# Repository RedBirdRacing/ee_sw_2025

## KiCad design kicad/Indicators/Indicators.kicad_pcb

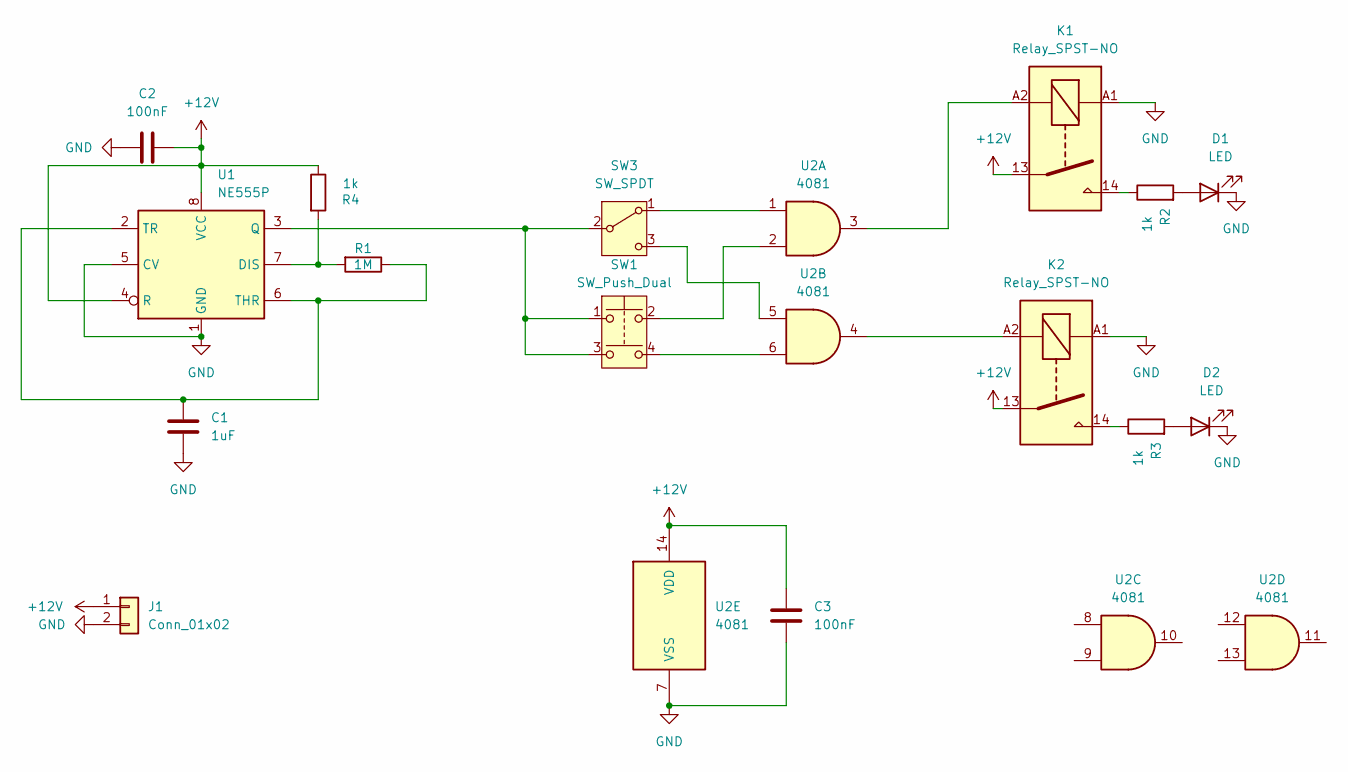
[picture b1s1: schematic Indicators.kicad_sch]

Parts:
C1: 1uF; C_0805_2012Metric_Pad1.18x1.45mm_HandSolder
C2, C3: 100nF; C_0805_2012Metric_Pad1.18x1.45mm_HandSolder
D1, D2: LED; LED_0805_2012Metric_Pad1.15x1.40mm_HandSolder
J1: Conn_01x02; JST_XH_B2B-XH-A_1x02_P2.50mm_Vertical
K1, K2: Relay_SPST-NO; JST_XH_B4B-XH-A_1x04_P2.50mm_Vertical
R1: 1M; R_Axial_DIN0204_L3.6mm_D1.6mm_P5.08mm_Horizontal
R2, R3, R4: 1k; R_Axial_DIN0204_L3.6mm_D1.6mm_P5.08mm_Horizontal
SW1: SW_Push_Dual; JST_XH_B4B-XH-A_1x04_P2.50mm_Vertical
SW3: SW_SPDT; JST_XH_B3B-XH-A_1x03_P2.50mm_Vertical
U1: NE555P; DIP-8_W7.62mm
U2: 4081; DIP-14_W7.62mm

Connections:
+12V: C2.2, C3.2, J1.1, K1.13, K2.13, R4.1, U1.4 (R), U1.8 (VCC), U2.14 (VDD)
GND: C1.2, C2.1, C3.1, D1.1 (K), D2.1 (K), J1.2, K1.A1, K2.A1, U1.1 (GND), U1.5 (CV), U2.7 (VSS)
unnamed: D1.2 (A), R2.2
unnamed: D2.2 (A), R3.2
unnamed: K1.14, R2.1
unnamed: K1.A2, U2.3
unnamed: K2.14, R3.1
unnamed: K2.A2, U2.4
unnamed: SW1.2, U2.2
unnamed: SW1.4, U2.6
unnamed: SW3.1 (A), U2.1
unnamed: SW1.1, SW1.3, SW3.2 (B), U1.3 (Q)
unnamed: SW3.3 (C), U2.5
unnamed: R1.2, R4.2, U1.7 (DIS)
unnamed: C1.1, R1.1, U1.2 (TR), U1.6 (THR)

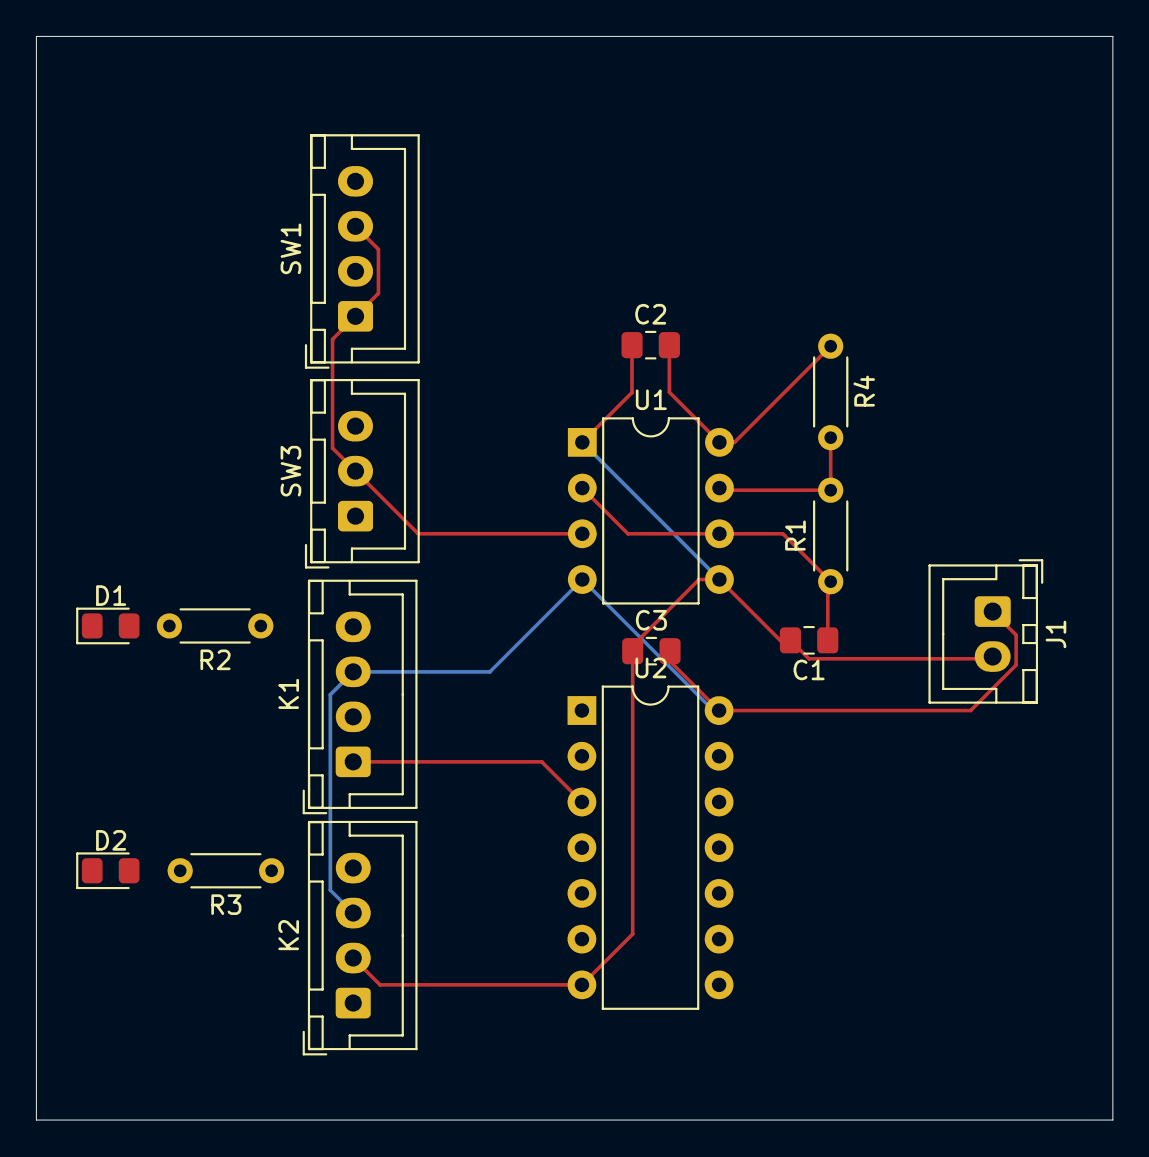
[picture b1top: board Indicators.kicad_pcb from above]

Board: 2 copper layers, 59.8 x 60.2 mm, 16 parts (0 on the bottom side), 15 nets.

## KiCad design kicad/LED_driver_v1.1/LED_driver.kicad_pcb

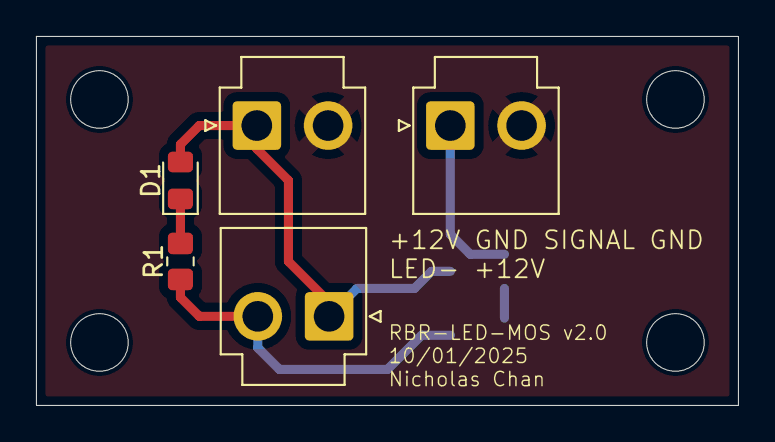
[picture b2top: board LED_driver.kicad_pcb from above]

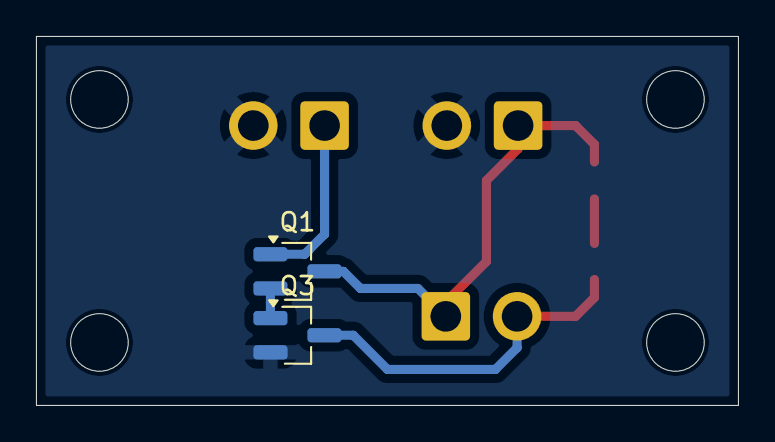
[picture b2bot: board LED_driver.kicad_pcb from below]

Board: 2 copper layers, 39.0 x 20.5 mm, 11 parts (2 on the bottom side), 6 nets.

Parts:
D1: LED; LED_0805_2012Metric_Pad1.15x1.40mm_HandSolder
H1, H2, H3, H4: MountingHole; MountingHole_3.2mm_M3
J1, J2, J3: Conn_01x02; JST_VH_B2P-VH_1x02_P3.96mm_Vertical
Q1: MMBT3904; SOT-23_Handsoldering
Q3: 2N7002; SOT-23_Handsoldering
R1: 1k; R_0805_2012Metric_Pad1.20x1.40mm_HandSolder

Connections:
+12V: D1.2 (A), J1.1, J3.1, Q1.3 (C)
/LED-: J3.2, Q3.3 (D), R1.2
/SIGNAL: J2.1, Q1.1 (B)
GND: J1.2, J2.2, Q3.2 (S)
unnamed: D1.1 (K), R1.1
unnamed: Q1.2 (E), Q3.1 (G)

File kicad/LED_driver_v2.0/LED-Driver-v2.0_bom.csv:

"Value","Footprint","Qty"
"LED","LED_SMD:LED_0805_2012Metric_Pad1.15x1.40mm_HandSolder","1"
"Conn_01x02","Connector_JST:JST_VH_B2P-VH_1x02_P3.96mm_Vertical","3"
"MMBT3904","Package_TO_SOT_SMD:SOT-23_Handsoldering","1"
"2N7002","Package_TO_SOT_SMD:SOT-23_Handsoldering","1"
"1k","Resistor_SMD:R_0805_2012Metric_Pad1.20x1.40mm_HandSolder","1"

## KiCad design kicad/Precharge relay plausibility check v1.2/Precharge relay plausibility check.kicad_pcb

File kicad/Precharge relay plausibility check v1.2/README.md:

v1.2 changed screw holes from M2 to M3 by Nicholas

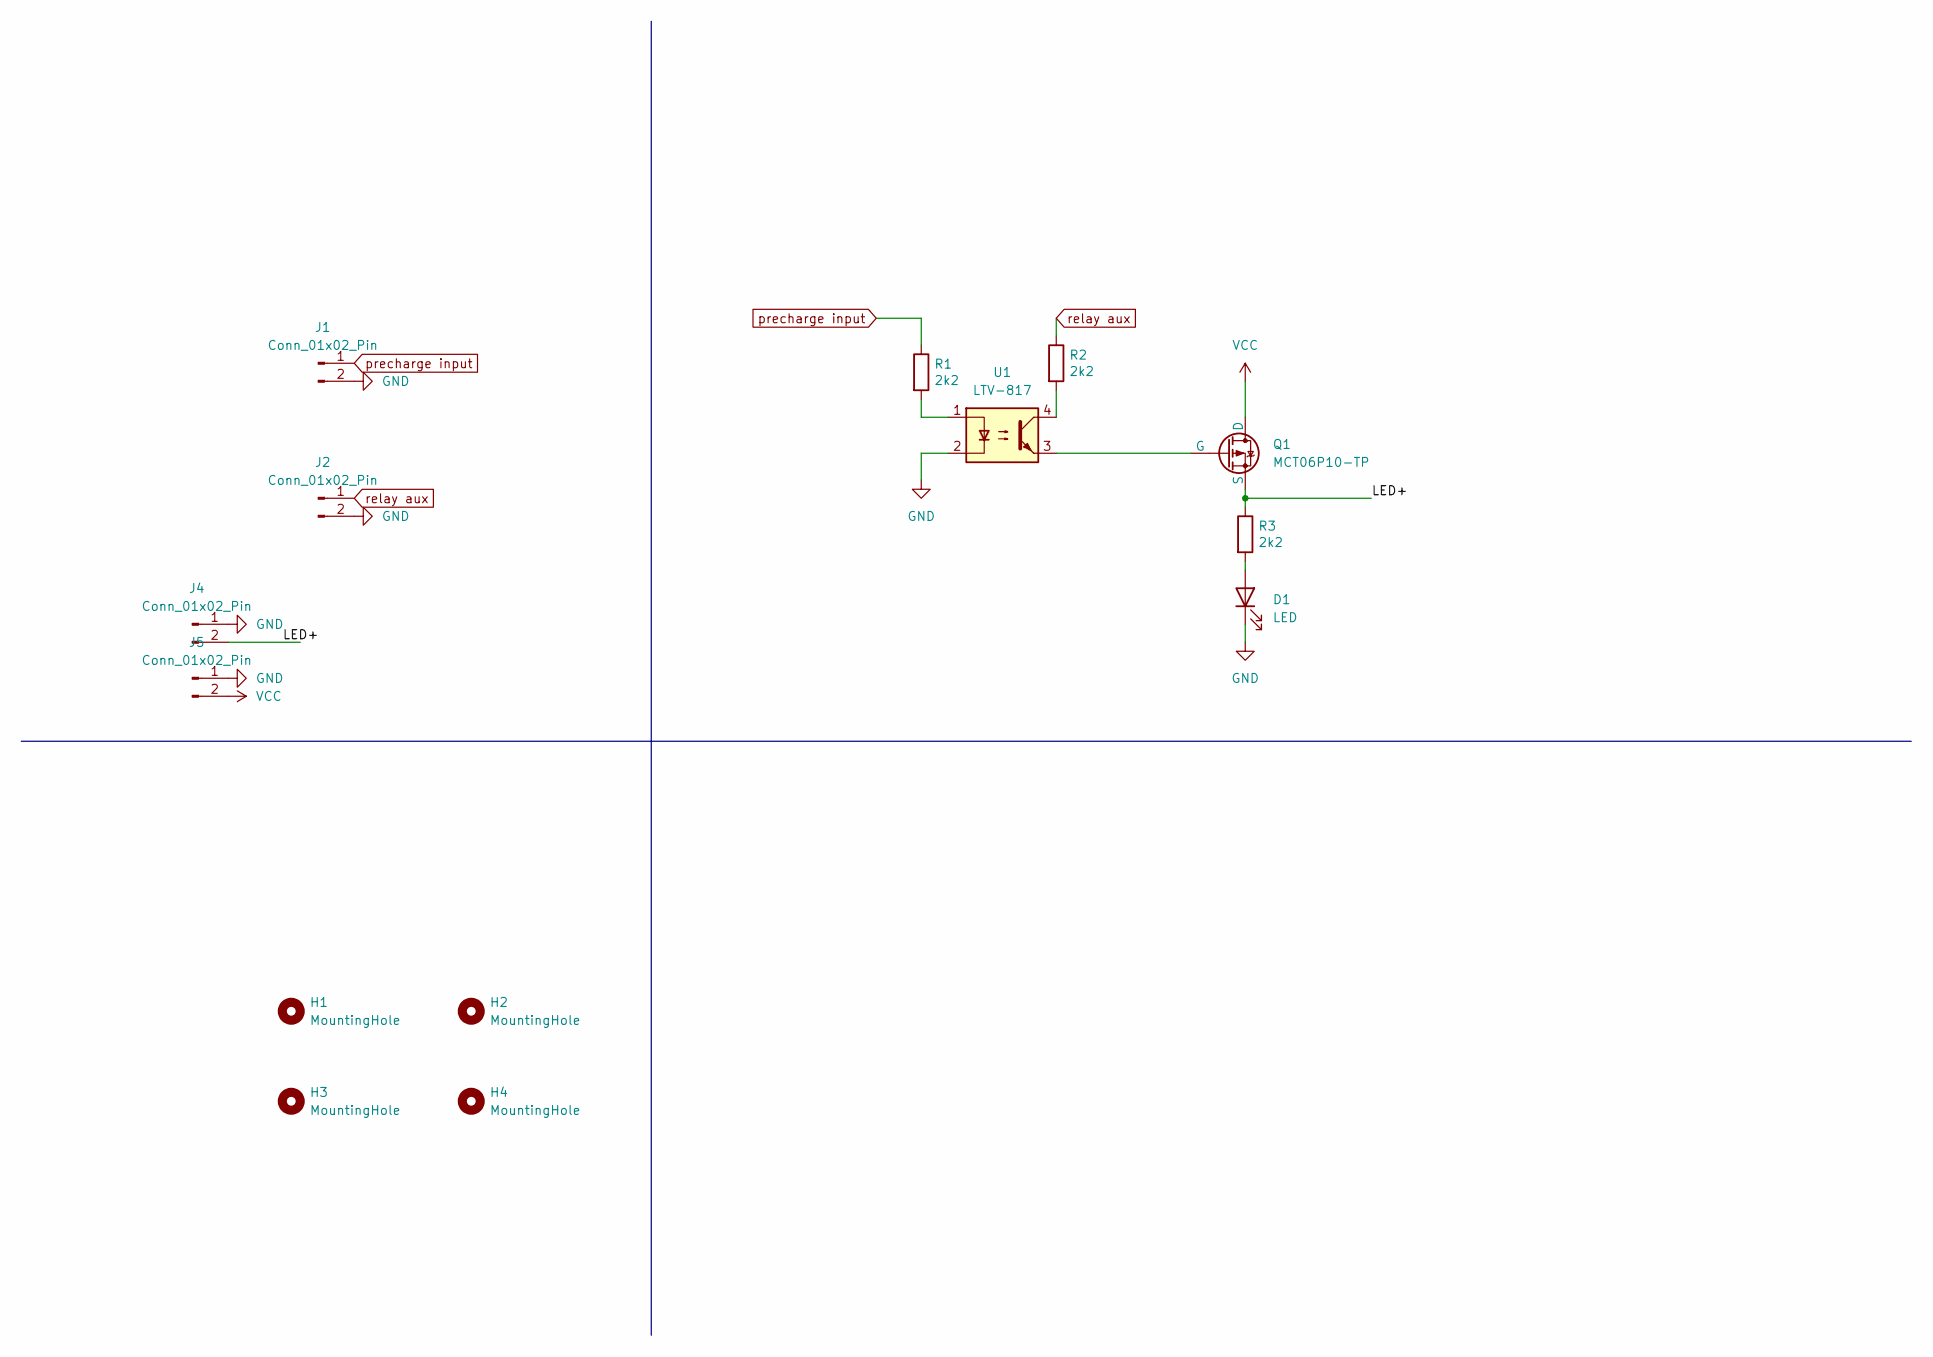
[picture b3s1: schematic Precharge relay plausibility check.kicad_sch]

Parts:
D1: LED; LED_0805_2012Metric_Pad1.15x1.40mm_HandSolder
H1, H2, H3, H4: MountingHole; MountingHole_3.2mm_M3
J1, J2, J4, J5: Conn_01x02_Pin; JST_VH_B2P-VH_1x02_P3.96mm_Vertical
Q1: MCT06P10-TP; SOT-223-3_TabPin2
R1, R2, R3: 2k2; R_0805_2012Metric_Pad1.20x1.40mm_HandSolder
U1: LTV-817; DIP-4_W7.62mm

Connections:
/LED+: J4.2, Q1.3 (S), R3.1
GND: D1.1 (K), J1.2, J2.2, J4.1, J5.1, U1.2
unnamed: D1.2 (A), R3.2
unnamed: Q1.2 (G), U1.3
unnamed: R1.2, U1.1
unnamed: R2.2, U1.4
VCC: J5.2, Q1.1 (D)
precharge input: J1.1, R1.1
relay aux: J2.1, R2.1

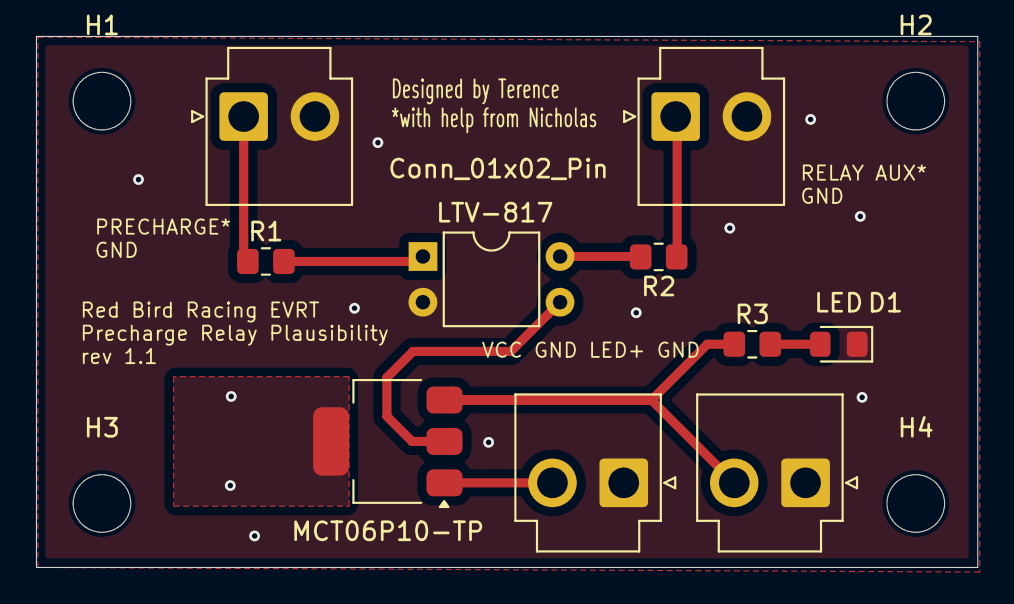
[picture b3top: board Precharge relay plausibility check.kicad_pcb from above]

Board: 2 copper layers, 52.3 x 29.5 mm, 14 parts (0 on the bottom side), 9 nets.

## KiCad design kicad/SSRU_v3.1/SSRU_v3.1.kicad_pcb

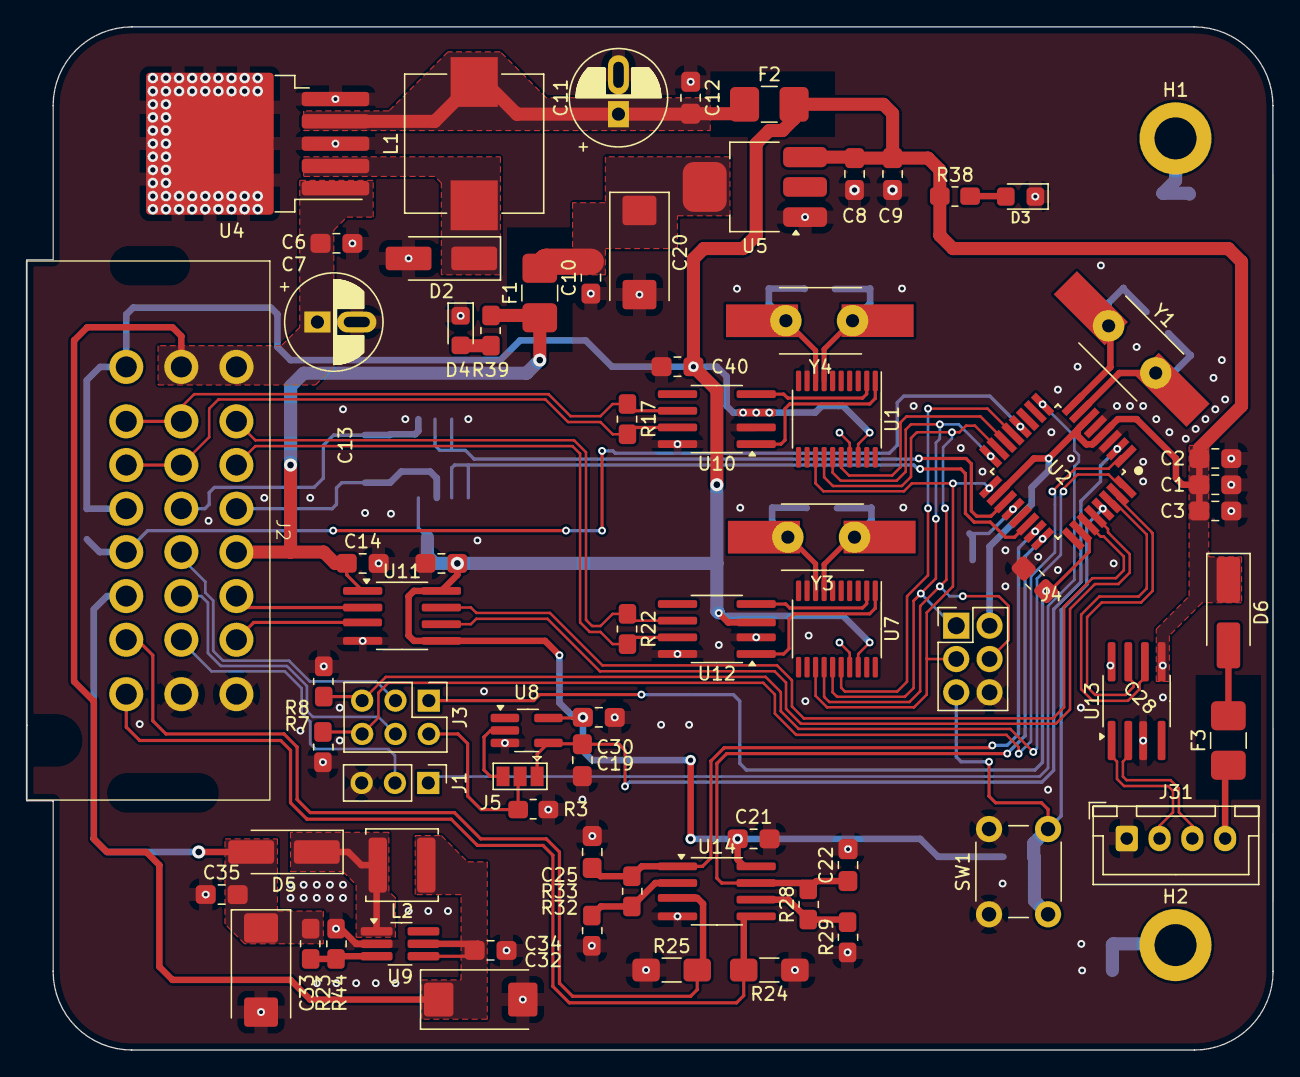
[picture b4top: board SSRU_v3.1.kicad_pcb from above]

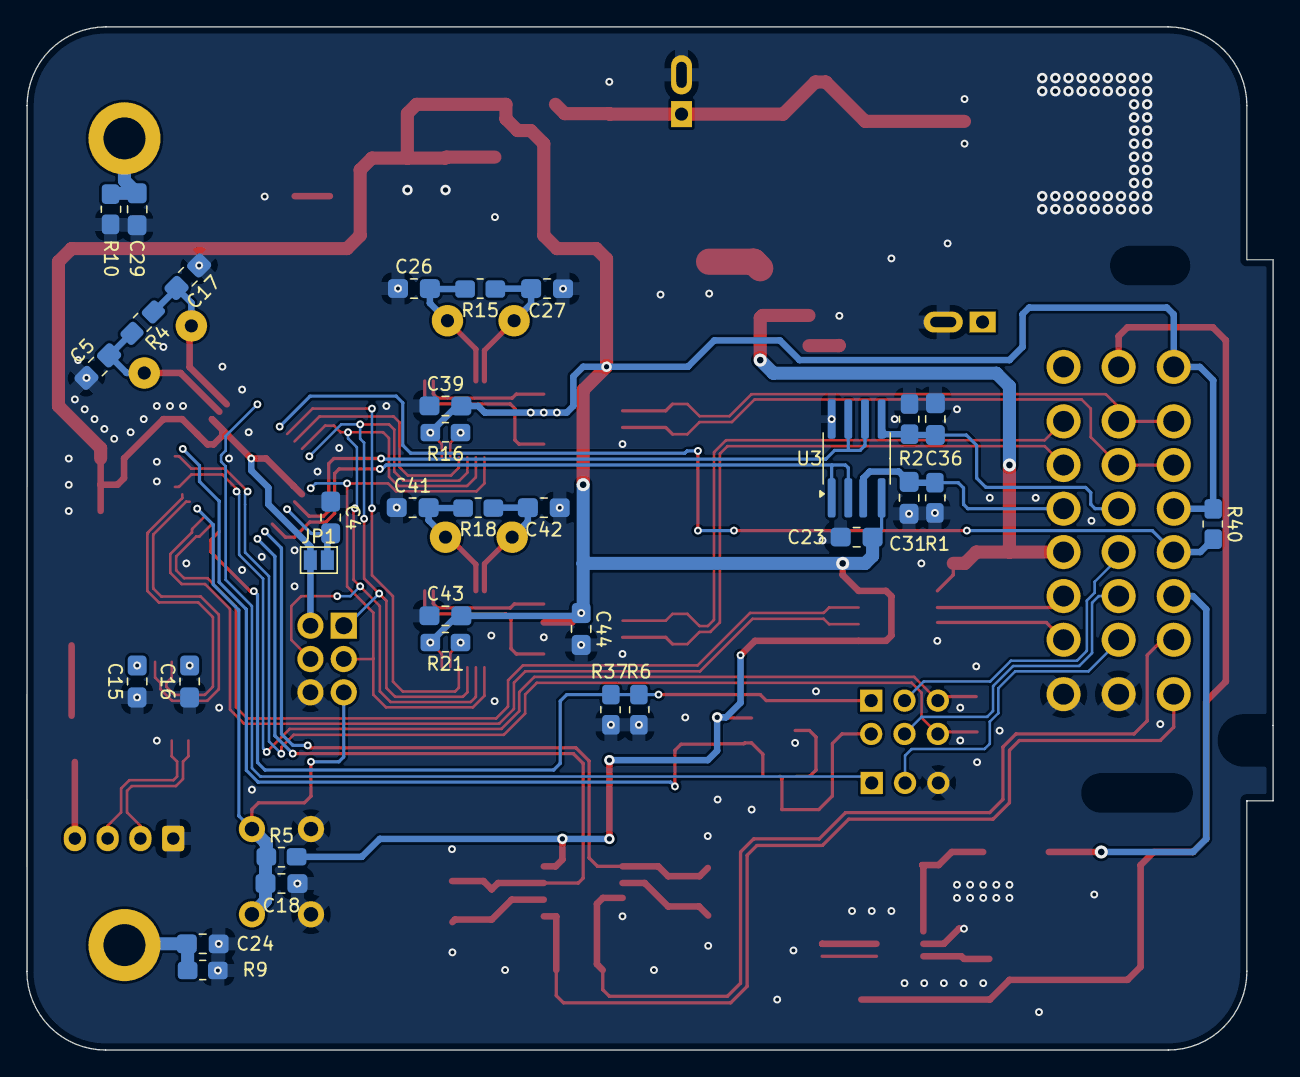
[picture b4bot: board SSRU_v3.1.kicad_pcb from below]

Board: 2 copper layers, 95.0 x 78.0 mm, 106 parts (33 on the bottom side), 69 nets.

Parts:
C1, C3, C4, C6, C8, C10, C12, C13, C14, C15, C16, C21, C22, C23, C24, C25, C28, C29, C30, C31, C34, C35, C36, C39, C40, C43, C44: 100nF; C_0805_2012Metric_Pad1.18x1.45mm_HandSolder_L
C2, C9, C18: 10uF; C_0805_2012Metric_Pad1.18x1.45mm_HandSolder_L
C5, C17, C26, C27, C41, C42: 22pF; C_0805_2012Metric_Pad1.18x1.45mm_HandSolder_L
C7: 100uF; CP_Radial_D6.3mm_P2.50mm_handsolder
C11: 330uF; CP_Radial_D6.3mm_P2.50mm_handsolder
C19: optional; C_0805_2012Metric_Pad1.18x1.45mm_HandSolder_L
C20, C32, C33: 22uF; CP_EIA-7343-30_AVX-N_HandSolder
D2, D5, D6: SMA Diode; D_SMA_Handsoldering
D3, D4: LED; LED_0805_2012Metric_Pad1.45x1.40mm_HandSolder
F1, F2, F3: Fuse; Fuse_1210_3225Metric_Pad1.42x2.65mm_HandSolder
H1, H2: MountingHole_Pad; MountingHole_3.2mm_M3_ISO14580_Pad
J1: Conn_01x03; PinHeader_1x03_P2.54mm_Vertical
J2: Conn_01x24; HD241_24pin
J3: Conn_02x03_Odd_Even; PinHeader_2x03_P2.54mm_Vertical
J4: AVR-ISP-6; PinHeader_2x03_P2.54mm_Vertical
J5: Conn_01x03; SolderJumper-3_P1.3mm_Open_Pad1.0x1.5mm
J31: Conn_01x04; JST_XH_B4B-XH-A_1x04_P2.50mm_Vertical
JP1: Jumper_2_Open; SolderJumper-2_P1.3mm_Open_Pad1.0x1.5mm
L1: 330uH; L_10.4x10.4_H4.8
L2: 4.7-22uH; L_Sunlord_SWPA5040S
R1, R2, R3, R6, R7, R8, R9, R10: 1M; R_0805_2012Metric_Pad1.20x1.40mm_HandSolder_L
R4, R15, R18: 10M; R_0805_2012Metric_Pad1.20x1.40mm_HandSolder_L
R5: 4.7k; R_0805_2012Metric_Pad1.20x1.40mm_HandSolder_L
R16, R21: 10k; R_0805_2012Metric_Pad1.20x1.40mm_HandSolder_L
R17, R22, R39: 120R; R_0805_2012Metric_Pad1.20x1.40mm_HandSolder_L
R23: 249k; R_0805_2012Metric_Pad1.20x1.40mm_HandSolder_L
R24, R25: 10R; R_1206_3216Metric_Pad1.30x1.75mm_HandSolder_RMC
R28, R33: 22k; R_0805_2012Metric_Pad1.20x1.40mm_HandSolder_L
R29, R32: 1k; R_0805_2012Metric_Pad1.20x1.40mm_HandSolder_L
R37: 50k; R_0805_2012Metric_Pad1.20x1.40mm_HandSolder_L
R38: 330R; R_0805_2012Metric_Pad1.20x1.40mm_HandSolder_L
R40: 4k7; R_0805_2012Metric_Pad1.20x1.40mm_HandSolder_L
R44: 680R; R_0805_2012Metric_Pad1.20x1.40mm_HandSolder_L
SW1: SW_Push; SW_PUSH_6mm_H5mm
U1, U7: MCP2515-xSO; TSSOP-20_4.4x6.5mm_P0.65mm
U2: ATmega328P-A; TQFP-32_7x7mm_P0.8mm_L
U3, U14: LM2904; SOIC-8_3.9x4.9mm_P1.27mm_RMC_Handsolder
U4: LM2576S-5; TO-263-5_TabPin3_Handsolder
U5: AMS1117-3.3; SOT-223-3_TabPin2_Handsolder
U8: 74LVC1G17; SOT-23-5_HandSoldering_Extended_RMC
U9: MT3608/SDB628; SOT-23-6_Handsoldering_Extended_RMC
U10, U12: TJA1051T; SOIC-8_3.9x4.9mm_P1.27mm_RMC_Handsolder
U11: TCA9517D; SOIC-8_3.9x4.9mm_P1.27mm_RMC_Handsolder
U13: CH340N; SOIC-8_3.9x4.9mm_P1.27mm_RMC_Handsolder
Y1: 16MHz; Crystal_HC49-U_Vertical_W_SMD
Y3, Y4: 20MHz; Crystal_HC49-U_Vertical_W_SMD

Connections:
328+: U2.30 (PD0), U13.6 (TXD)
328-: U2.31 (PD1), U13.7 (RXD)
+3.3V: C14.1, F1.1, J2.5, R39.1, U11.1 (VCCA)
+5V: C1.2, C2.2, C3.2, C8.2, C9.2, C13.2, C15.2, C21.1, C23.2, C30.2, C39.2, C40.1, C43.2, C44.1, D6.1 (K), F2.2, J2.17, J2.20, J4.2 (VCC), JP1.1 (A), R5.2, R16.2, R21.2, R38.1, R40.1, U1.18 (VDD), U2.4 (VCC), U2.6 (VCC), U2.18 (AVCC), U3.4 (V-), U5.3 (VI), U7.18 (VDD), U8.5 (VCC), U10.3 (VCC), U11.5 (EN), U11.8 (VCCB), U12.3 (VCC), U13.5 (VCC), U14.8 (V+)
+12V: C6.2, C7.1, C32.1, C34.2, J2.1, J2.9, L2.1, U4.1 (VIN), U9.4 (EN), U9.5 (IN)
+24V: C33.1, C35.2, D5.2 (A), J2.22, R23.1
BRAKE_TEMP1: J2.23, R25.2, U14.3 (+)
BRAKE_TEMP2: J2.24, R24.2, U14.5 (+)
BRAKE_TEMP_OUT1: C25.1, R33.2, U2.23 (PC0), U14.1
BRAKE_TEMP_OUT2: C22.1, R28.2, U2.24 (PC1), U14.7
CAN1+: J2.11, J2.19, R17.2, U10.7 (CANH)
CAN1-: J2.10, J2.18, R17.1, U10.6 (CANL)
CAN2+: J2.3, R22.2, U12.7 (CANH)
CAN2-: J2.2, R22.1, U12.6 (CANL)
CS_CAN1: U1.16 (~CS), U2.14 (PB2)
CS_CAN2: U2.13 (PB1), U7.16 (~CS)
DS18B20: J2.21, R40.2, U2.12 (PB0)
ENCODER+: J3.5, R8.2, U2.32 (PD2)
ENCODER-: J3.6, R7.2, U2.1 (PD3)
FLOW_IN: J3.2, J5.2, R3.2
FLOW_OUT: C19.2, J5.1, U2.2 (PD4), U8.4
GND: C1.1, C2.1, C3.1, C4.1, C5.1, C6.1, C7.2, C8.1, C9.1, C10.1, C11.2, C12.1, C13.1, C14.2, C15.1, C16.1, C17.1, C18.1, C19.1, C20.2, C21.2, C22.2, C23.1, C24.1, C25.2, C26.1, C27.1, C28.2, C29.1, C30.1, C31.1, C32.2, C33.2, C34.1, C35.1, C36.1, C39.1, C40.2, C41.1, C42.1, C43.1, C44.2, D2.2 (A), D3.1 (K), D4.1 (K), J1.3, J2.8, J2.16, J4.6 (GND), J31.1, R1.1, R2.1, R3.1, R6.1, R7.1, R8.1, R9.1, R10.1, R24.1, R25.1, R29.1, R32.1, R37.2, R44.2, SW1.1, U1.9 (VSS), U2.3 (GND), U2.5 (GND), U2.21 (GND), U3.8 (V+), U4.3 (GND), U4.5 (~ON/OFF), U5.1 (GND), U7.9 (VSS), U8.3 (GND), U9.2 (GND), U10.2 (GND), U10.8 (S), U11.4 (GND), U12.2 (GND), U12.8 (S), U13.3 (GND), U14.4 (V-)
GND1: C29.2, H1.1, R10.2
GND2: C24.2, H2.1, R9.2
I2C+: U2.27 (PC4), U11.7 (SCLB)
I2C-: U2.28 (PC5), U11.6 (SDAB)
MISO: J4.1 (MISO), U1.15 (SO), U2.16 (PB4), U7.15 (SO)
MOSI: J4.4 (MOSI), U1.14 (SI), U2.15 (PB3), U7.14 (SI)
unnamed: C10.2, C20.1, F1.2, U5.2 (VO)
unnamed: D2.1 (K), L1.1, U4.2 (OUT)
unnamed: D3.2 (A), R38.2
unnamed: D4.2 (A), R39.2
unnamed: D5.1 (K), L2.2, U9.1 (SW)
unnamed: D6.2 (A), F3.2
unnamed: J5.3, U8.2
unnamed: F3.1, J31.4
unnamed: C4.2, JP1.2 (B), U2.20 (AREF)
unnamed: C27.2, R15.1, U1.8 (OSC1), Y4.2
unnamed: C26.2, R15.2, U1.7 (OSC2), Y4.1
unnamed: U1.2 (RXCAN), U10.4 (RXD)
unnamed: U1.1 (TXCAN), U10.1 (TXD)
unnamed: R16.1, U1.17 (~RESET)
unnamed: C11.1, C12.2, F2.1, L1.2, U4.4 (FB)
unnamed: C42.2, R18.1, U7.8 (OSC1), Y3.2
unnamed: C41.2, R18.2, U7.7 (OSC2), Y3.1
unnamed: R21.1, U7.17 (~RESET)
unnamed: R23.2, R44.1, U9.3 (FB)
unnamed: U7.2 (RXCAN), U12.4 (RXD)
unnamed: U7.1 (TXCAN), U12.1 (TXD)
unnamed: C16.2, U13.8 (V3)
unnamed: R32.2, R33.1, U14.2 (-)
unnamed: R28.1, R29.2, U14.6 (-)
POT1_IN: C31.2, J2.4, R1.2, U3.3 (+)
POT1_OUT: U2.22 (ADC7), U3.1, U3.2 (-)
POT2_IN: C36.2, J2.12, R2.2, U3.5 (+)
POT2_OUT: U2.19 (ADC6), U3.6 (-), U3.7
PUMP_NTC_50k: C28.1, J3.1, R6.2, R37.1, U2.26 (PC3)
PUMP_PWM: J1.1, U2.9 (PD5)
RST: C18.2, J4.5 (~RST), R5.1, SW1.2, U2.29 (~RESET/PC6)
SCK: J4.3 (SCK), U1.13 (SCK), U2.17 (PB5), U7.13 (SCK)
SCL_3V3: J2.6, U11.2 (SCLA)
SDA_3V3: J2.7, U11.3 (SDAA)
UD+: J31.2, U13.1 (UD+)
UD-: J31.3, U13.2 (UD-)
XTAL1: C5.2, R4.2, U2.7 (XTAL1/PB6), Y1.2
XTAL2: C17.2, R4.1, U2.8 (XTAL2/PB7), Y1.1
j1: J2.13, J3.3
j2: J2.14, J3.4
j3: J1.2, J2.15

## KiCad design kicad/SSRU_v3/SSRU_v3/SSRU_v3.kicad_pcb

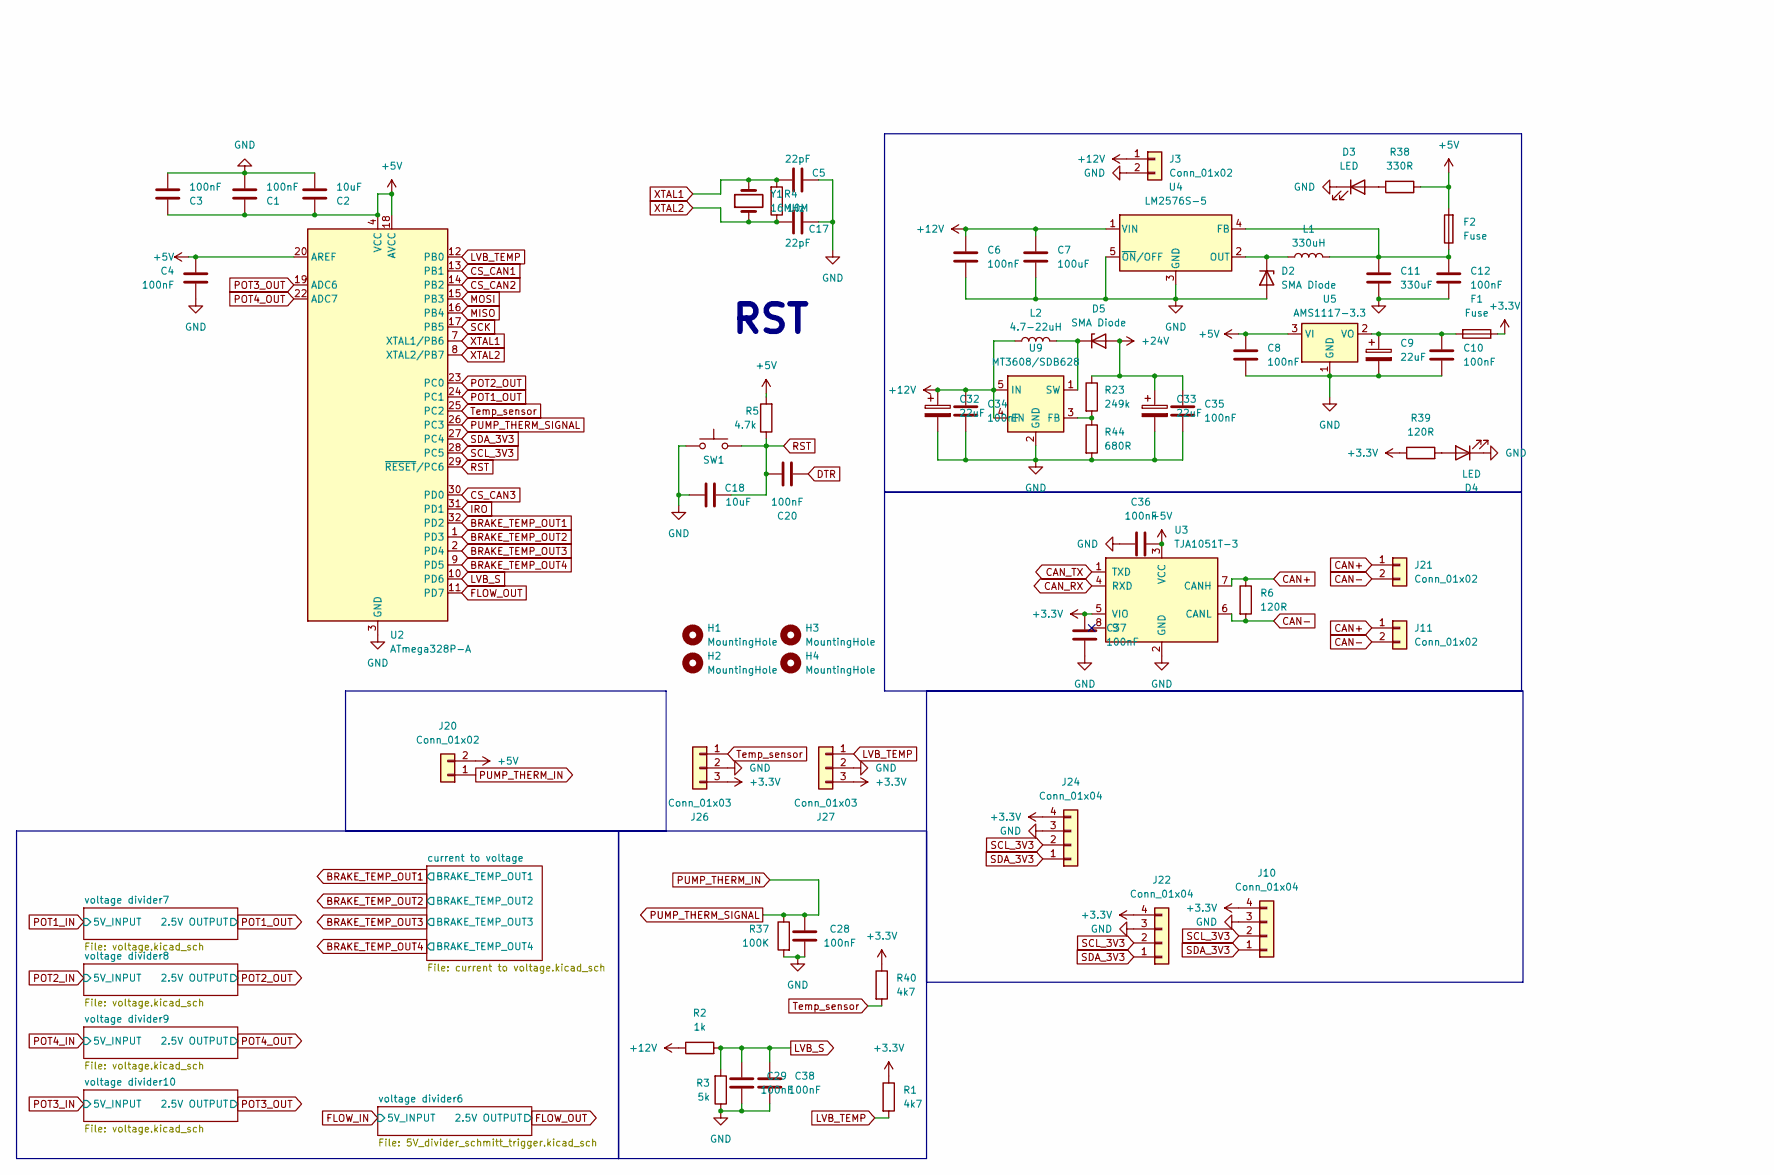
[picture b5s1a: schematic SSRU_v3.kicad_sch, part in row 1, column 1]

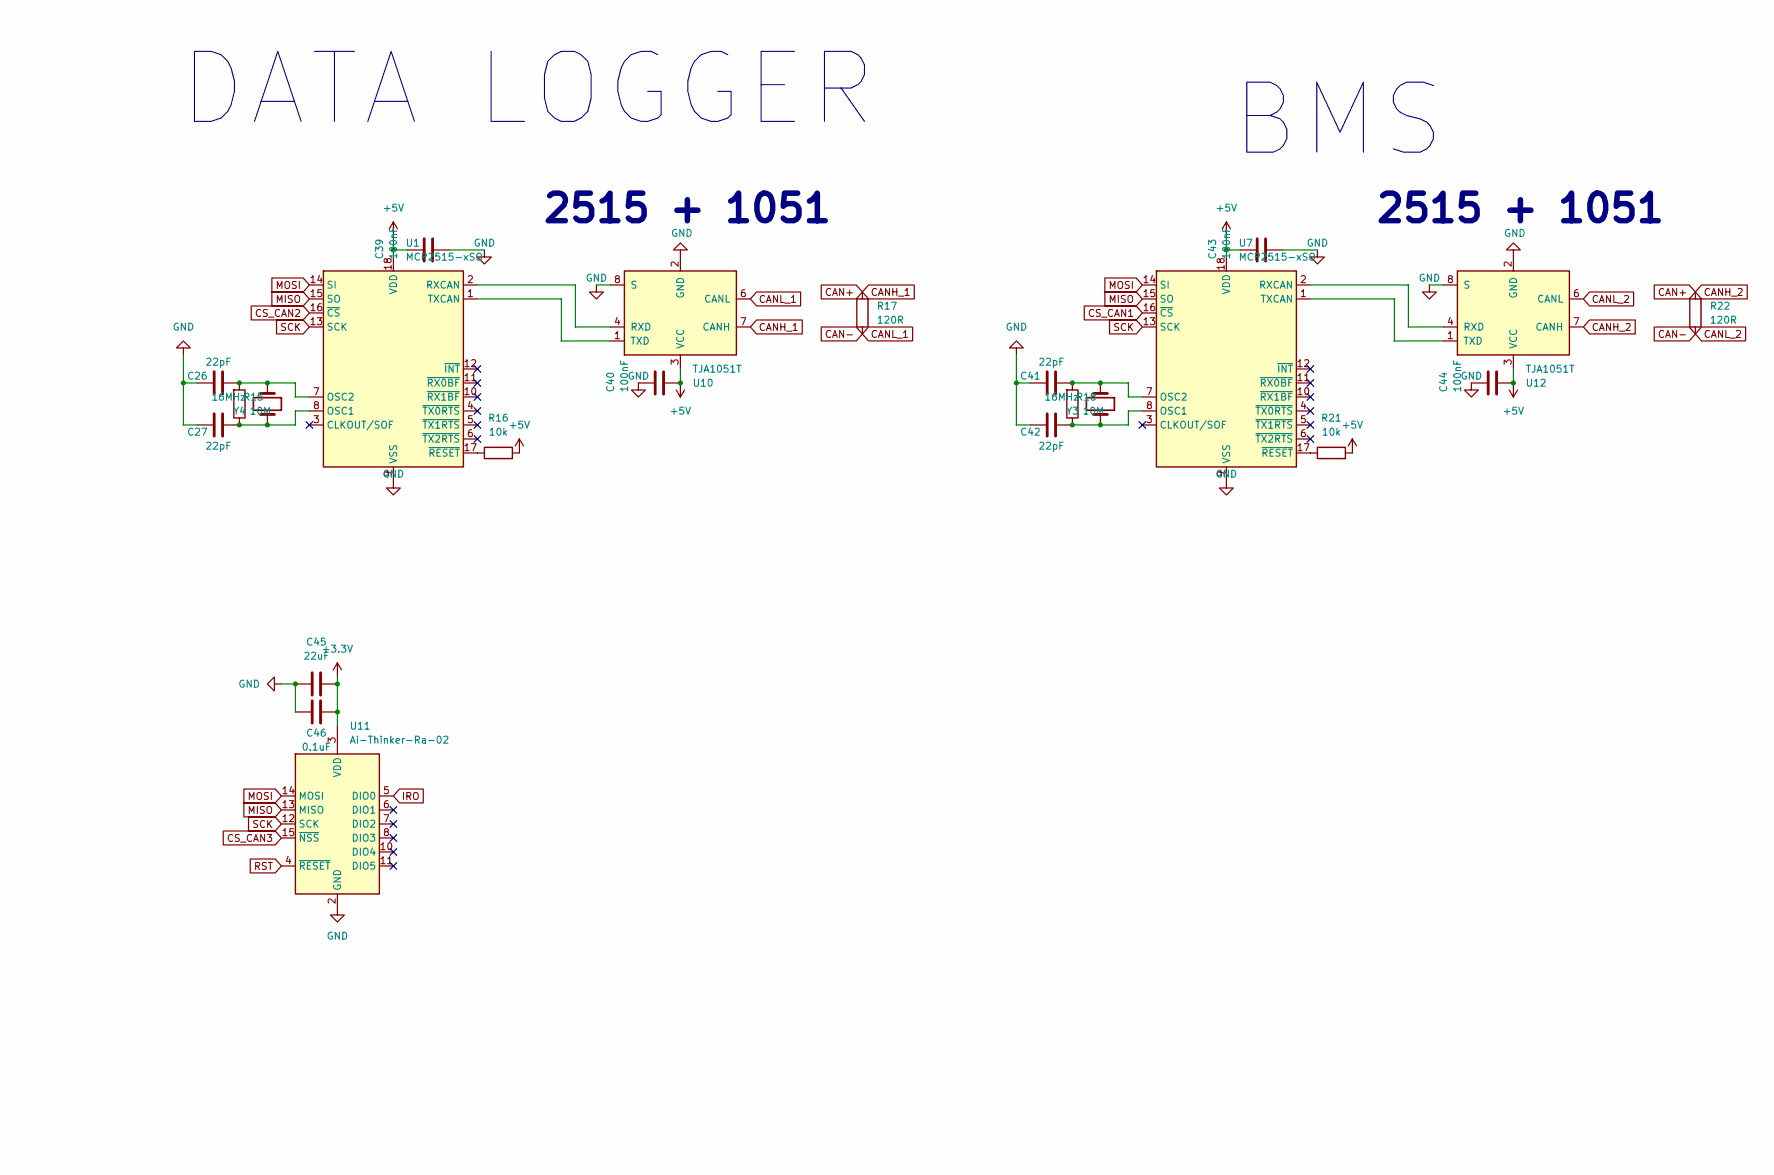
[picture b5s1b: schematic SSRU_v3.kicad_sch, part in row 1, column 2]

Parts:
C1, C3, C4, C6, C8, C10, C12, C20, C28, C29, C34, C35, C36, C37, C38, C39, C40, C43, C44: 100nF; C_0805_2012Metric_Pad1.18x1.45mm_HandSolder_L
C2, C18: 10uF; C_0805_2012Metric_Pad1.18x1.45mm_HandSolder_L
C5, C17, C26, C27, C41, C42: 22pF; C_0805_2012Metric_Pad1.18x1.45mm_HandSolder_L
C7: 100uF; CP_Radial_D6.3mm_P2.50mm
C9, C45: 22uF; C_0805_2012Metric_Pad1.18x1.45mm_HandSolder_L
C11: 330uF; CP_Radial_D6.3mm_P2.50mm
C32, C33: 22uF; CP_EIA-3528-15_AVX-H_Pad1.50x2.35mm_HandSolder_RMC
C46: 0.1uF; C_0805_2012Metric_Pad1.18x1.45mm_HandSolder_L
D2, D5: SMA Diode; D_SMA_Handsoldering
D3, D4: LED; LED_0805_2012Metric_Pad1.45x1.40mm_HandSolder
F1, F2: Fuse; Fuse_1210_3225Metric_Pad1.42x2.65mm_HandSolder
H1, H2, H3, H4: MountingHole; MountingHole_3.2mm_M3
J3: Conn_01x02; JST_VH_B2P-VH_1x02_P3.96mm_Vertical
J10, J22, J24: Conn_01x04; JST_XH_B4B-XH-A_1x04_P2.50mm_Vertical
J11, J20, J21: Conn_01x02; JST_XH_B2B-XH-A_1x02_P2.50mm_Vertical
J26, J27: Conn_01x03; JST_XH_B3B-XH-A_1x03_P2.50mm_Vertical
L1: 330uH; L_10.4x10.4_H4.8
L2: 4.7-22uH; L_Wuerth_HCI-5040
R1, R40: 4k7; R_0805_2012Metric_Pad1.20x1.40mm_HandSolder_L
R2: 1k; R_0805_2012Metric_Pad1.20x1.40mm_HandSolder_L
R3: 5k; R_0805_2012Metric_Pad1.20x1.40mm_HandSolder_L
R4, R15, R18: 10M; R_0805_2012Metric_Pad1.20x1.40mm_HandSolder_L
R5: 4.7k; R_0805_2012Metric_Pad1.20x1.40mm_HandSolder_L
R6, R17, R22, R39: 120R; R_0805_2012Metric_Pad1.20x1.40mm_HandSolder_L
R16, R21: 10k; R_0805_2012Metric_Pad1.20x1.40mm_HandSolder_L
R23: 249k; R_0805_2012Metric_Pad1.20x1.40mm_HandSolder_L
R37: 100K; R_0805_2012Metric_Pad1.20x1.40mm_HandSolder_L
R38: 330R; R_0805_2012Metric_Pad1.20x1.40mm_HandSolder_L
R44: 680R; R_0805_2012Metric_Pad1.20x1.40mm_HandSolder_L
SW1: SW_Push; SW_PUSH_6mm_H5mm
U1, U7: MCP2515-xSO; TSSOP-20_4.4x6.5mm_P0.65mm
U2: ATmega328P-A; TQFP-32_7x7mm_P0.8mm
U3: TJA1051T-3; SOIC-8_3.9x4.9mm_P1.27mm_RMC_Handsolder
U4: LM2576S-5; TO-263-5_TabPin3_Handsolder
U5: AMS1117-3.3; SOT-223-3_TabPin2_Handsolder
U9: MT3608/SDB628; SOT-23-6_Handsoldering
U10, U12: TJA1051T; SOIC-8_3.9x4.9mm_P1.27mm_RMC_Handsolder
U11: Ai-Thinker-Ra-02; Ai-Thinker-Ra-01-LoRa
Y1, Y3, Y4: 16MHz; Crystal_HC49-U_Vertical_W_SMD

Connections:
+3.3V: C37.2, C45.2, C46.1, F1.1, J10.4, J22.4, J24.4, J26.3, J27.3, R1.1, R39.1, R40.1, U3.5 (VIO), U11.3 (VDD); also elsewhere on the board
+5V: C1.2, C2.2, C3.2, C4.2, C8.2, C36.1, C39.2, C40.1, C43.2, C44.1, F2.2, J20.2, R5.2, R16.2, R21.2, R38.1, U1.18 (VDD), U2.4 (VCC), U2.6 (VCC), U2.18 (AVCC), U2.20 (AREF), U3.3 (VCC), U5.3 (VI), U7.18 (VDD), U10.3 (VCC), U12.3 (VCC); also elsewhere on the board
+12V: C6.2, C7.1, C32.1, C34.2, J3.1, L2.1, R2.1, U4.1 (VIN), U9.4 (EN), U9.5 (IN)
+24V: C33.1, C35.2, D5.2 (A), R23.1; also elsewhere on the board
BRAKE_TEMP_OUT1: U2.32 (PD2); also elsewhere on the board
BRAKE_TEMP_OUT2: U2.1 (PD3); also elsewhere on the board
BRAKE_TEMP_OUT3: U2.2 (PD4); also elsewhere on the board
BRAKE_TEMP_OUT4: U2.9 (PD5); also elsewhere on the board
CAN+: J11.1, J21.1, R6.1, R17.2, R22.2, U3.7 (CANH), U10.7 (CANH), U12.7 (CANH)
CAN-: J11.2, J21.2, R6.2, R17.1, R22.1, U3.6 (CANL), U10.6 (CANL), U12.6 (CANL)
CAN_RX: U3.4 (RXD)
CAN_TX: U3.1 (TXD)
CS_CAN1: U2.13 (PB1), U7.16 (~CS)
CS_CAN2: U1.16 (~CS), U2.14 (PB2)
CS_CAN3: U2.30 (PD0), U11.15 (~NSS)
DTR: C20.1
FLOW_OUT: U2.11 (PD7); also elsewhere on the board
GND: C1.1, C2.1, C3.1, C4.1, C5.1, C6.1, C7.2, C8.1, C9.2, C10.1, C11.2, C12.1, C17.1, C18.1, C26.1, C27.1, C28.2, C29.2, C32.2, C33.2, C34.1, C35.1, C36.2, C37.1, C38.2, C39.1, C40.2, C41.1, C42.1, C43.1, C44.2, C45.1, C46.2, D2.2 (A), D3.1 (K), D4.1 (K), J3.2, J10.3, J22.3, J24.3, J26.2, J27.2, R3.1, R37.2, R44.2, SW1.1, U1.9 (VSS), U2.3 (GND), U2.5 (GND), U2.21 (GND), U3.2 (GND), U4.3 (GND), U4.5 (~ON/OFF), U5.1 (GND), U7.9 (VSS), U9.2 (GND), U10.2 (GND), U10.8 (S), U11.1 (GND), U11.2 (GND), U11.9 (GND), U11.16 (GND), U12.2 (GND), U12.8 (S); also elsewhere on the board
IRO: U2.31 (PD1), U11.5 (DIO0)
LVB_S: C29.1, C38.1, R2.2, R3.2, U2.10 (PD6)
LVB_TEMP: J27.1, R1.2, U2.12 (PB0)
MISO: U1.15 (SO), U2.16 (PB4), U7.15 (SO), U11.13 (MISO)
MOSI: U1.14 (SI), U2.15 (PB3), U7.14 (SI), U11.14 (MOSI)
unnamed: D2.1 (K), L1.1, U4.2 (OUT)
unnamed: D3.2 (A), R38.2
unnamed: D4.2 (A), R39.2
unnamed: D5.1 (K), L2.2, U9.1 (SW)
unnamed: C27.2, R15.1, U1.8 (OSC1), Y4.2
unnamed: C26.2, R15.2, U1.7 (OSC2), Y4.1
unnamed: U1.2 (RXCAN), U10.4 (RXD)
unnamed: U1.1 (TXCAN), U10.1 (TXD)
unnamed: R16.1, U1.17 (~RESET)
unnamed: C11.1, C12.2, F2.1, L1.2, U4.4 (FB)
unnamed: C9.1, C10.2, F1.2, U5.2 (VO)
unnamed: C42.2, R18.1, U7.8 (OSC1), Y3.2
unnamed: C41.2, R18.2, U7.7 (OSC2), Y3.1
unnamed: R21.1, U7.17 (~RESET)
unnamed: R23.2, R44.1, U9.3 (FB)
unnamed: U7.2 (RXCAN), U12.4 (RXD)
unnamed: U7.1 (TXCAN), U12.1 (TXD)
POT1_OUT: U2.24 (PC1); also elsewhere on the board
POT2_OUT: U2.23 (PC0); also elsewhere on the board
POT3_OUT: U2.19 (ADC6); also elsewhere on the board
POT4_OUT: U2.22 (ADC7); also elsewhere on the board
PUMP_THERM_IN: C28.1, J20.1, R37.1, U2.26 (PC3)
RST: C18.2, C20.2, R5.1, SW1.2, U2.29 (~RESET/PC6), U11.4 (~RESET)
SCK: U1.13 (SCK), U2.17 (PB5), U7.13 (SCK), U11.12 (SCK)
SCL_3V3: J10.2, J22.2, J24.2, U2.28 (PC5)
SDA_3V3: J10.1, J22.1, J24.1, U2.27 (PC4)
Temp_sensor: J26.1, R40.2, U2.25 (PC2)
XTAL1: C5.2, R4.2, U2.7 (XTAL1/PB6), Y1.2
XTAL2: C17.2, R4.1, U2.8 (XTAL2/PB7), Y1.1

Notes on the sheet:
DATA LOGGER
2515 + 1051
RST
BMS
